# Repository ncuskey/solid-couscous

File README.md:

# Christmas Lockboxes 🎄🔐

A distributed, synchronized Narrative Escape Room experience powered by ESP32, MQTT, and Web Technologies.

## 🚀 Features (V2 Release - Christmas 2024)

### 🎙️ Radio Play System
- **Synchronized Audio**: Three boxes play character-specific audio tracks in perfect sync
- **MQTT Coordination**: All boxes receive `play_intro` command and start playback after 2-second sync delay
- **ESP-NOW Backup**: Conductor (Box 1) can broadcast low-latency sync signals
- **Character Mapping**:
  - Box 1 = Sam (Conductor)
  - Box 2 = Kristine
  - Box 3 = Jacob

### 🎭 Radio Play Controller
- **`radio_play.html`**: Web interface for triggering synchronized playback
  - "Play on Boxes" - Sends MQTT command to all physical boxes
  - "Play All (Browser)" - Preview all tracks in browser
  - Individual track playback for testing
  - Live dialogue display with timestamps

### 🔌 Power Management
- **Smart Standby**: WiFi sleep disabled for audio streaming stability
- **Amp Shutdown**: Pin D14 controls MAX98357A enable/disable
- **LED Brightness Cap**: Hard limit at 50 (20%) to prevent brownouts

### 🏥 Health & Reliability
- **Self-Test**: Startup check for WiFi RSSI (> -75dBm)
- **Visual Feedback**:
    - 🟢🟢🟢 Green Pulse = Ready
    - 🔴🔴🔴 Red Pulse = Weak Signal / Error
- **OTA Updates**: All boxes support over-the-air firmware updates (password: `admin`)

## Hardware Config
- **Lockbox 1 (Sam)**: 192.168.7.199 (Conductor)
- **Lockbox 2 (Kristine)**: 192.168.7.201
- **Lockbox 3 (Jacob)**: 192.168.7.202
- **Server**: `167.172.211.213` (MQTT + Web)
- **MQTT Port:** 1883 (Device), 9001 (WebSockets)
- **Web App:** `http://167.172.211.213/xmasLockboxes/`
- **Radio Play:** `http://167.172.211.213/xmasLockboxes/radio_play.html`
- **Admin Panel:** `http://167.172.211.213/xmasLockboxes/admin.html`

## Setup for Multiple Boxes

### Firmware Configuration
Edit `ChristmasLockbox/ChristmasLockbox.ino` lines 34-36:
```cpp
// Box 1 = Sam (CONDUCTOR), Box 2 = Kristine, Box 3 = Jacob
const char* box_topic_cmd = "lockbox/1/cmd";    // Change 1 to 2 or 3
const char* box_topic_status = "lockbox/1/status";
const char* client_id = "box_1_v2";             // Change to box_2_v2 or box_3_v2
```

### OTA Firmware Update
```bash
# Compile
/opt/homebrew/bin/arduino-cli compile --fqbn esp32:esp32:esp32 \
  --libraries /path/to/xmasLockboxes/libraries \
  --output-dir /path/to/xmasLockboxes/ChristmasLockbox/build \
  /path/to/xmasLockboxes/ChristmasLockbox/ChristmasLockbox.ino

# Upload (replace IP with target box)
/opt/homebrew/bin/arduino-cli upload -p 192.168.7.199 \
  --fqbn esp32:esp32:esp32 \
  -i /path/to/xmasLockboxes/ChristmasLockbox/build/ChristmasLockbox.ino.bin \
  --upload-field password=admin
```

## Deployment
Deploy web updates to server:
```bash
scp -i ssh -r www/* root@167.172.211.213:/var/www/xmasLockboxes/
```

## Audio Files
Radio play audio files (in `www/audio/`):
- `Intro_Sam.mp3` - Box 1 character audio (Sam's lines only)
- `Intro_Kristine.mp3` - Box 2 character audio (Kristine's lines only)
- `Intro_Jacob.mp3` - Box 3 character audio (Jacob's lines only)

Timeline:
- 0-10s: Power-up sounds
- 10-15s: Settling/ambient
- 15s+: Dialogue begins (see `show_sequence.json` for exact timestamps)

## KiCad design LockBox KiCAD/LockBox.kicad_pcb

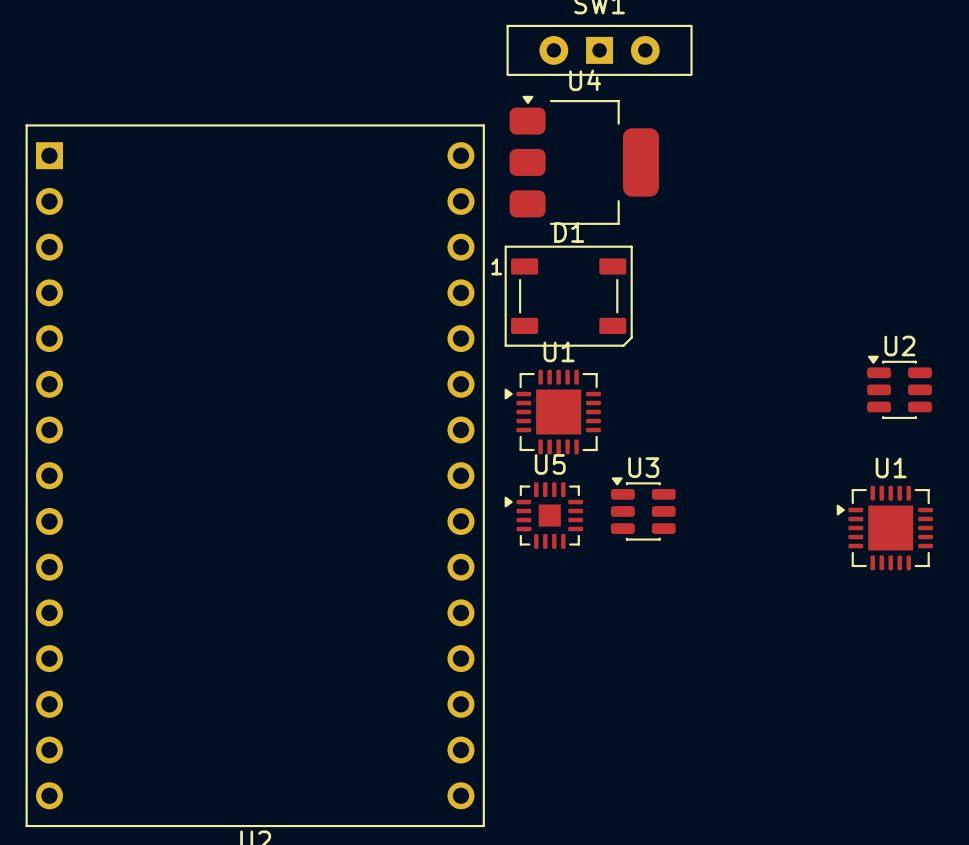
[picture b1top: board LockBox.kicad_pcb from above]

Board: 2 copper layers, 9 parts (0 on the bottom side), 10 nets, no tracks yet.

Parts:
D1: WS2812B; LED_WS2812B_PLCC4_5.0x5.0mm_P3.2mm
SW1: Power; SW_Slide-03_Wuerth-WS-SLTV_10x2.5x6.4_P2.54mm
U1, U1#2: MCP73871; QFN-20-1EP_4x4mm_P0.5mm_EP2.5x2.5mm
U2, U3: AP63203WU; TSOT-23-6
U2#2: ESP32-C3-DevKitM-1
U4: AMS1117-3.3; SOT-223-3_TabPin2
U5: MAX98357A; TQFN-16-1EP_3x3mm_P0.5mm_EP1.23x1.23mm

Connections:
/BAT+: U1.14 (V_{BAT}), U1.15 (V_{BAT})
/VBAT: U1#2.14 (V_{BAT}), U1#2.15 (V_{BAT}), U1#2.16 (V_{BAT_SENSE})
/VIN: U1.18 (IN), U1.19 (IN)
/VSYS: SW1.2 (C), U1.1 (OUT), U1.20 (OUT), U2.2 (EN), U2.3 (IN), U2#2.13 (5V), U2#2.14 (5V)
GND: U1.10 (V_{SS}), U1.11 (V_{SS}), U1.21 (V_{SS}), U1#2.5 (THERM), U1#2.9 (~TE), U1#2.10 (V_{SS}), U1#2.11 (V_{SS}), U1#2.21 (V_{SS}), U2.4 (GND), U2#2.1 (GND), U2#2.6 (GND), U2#2.8 (GND), U2#2.12 (GND), U2#2.15 (GND), U2#2.16 (GND), U2#2.19 (GND), U2#2.24 (GND), U2#2.27 (GND), U2#2.30 (GND)
unnamed: U2#2.2 (3V3), U2#2.3 (3V3)
unnamed: SW1.1 (B), U1#2.1 (OUT), U1#2.20 (OUT)
unnamed: U5.3 (GND), U5.11 (GND), U5.15 (GND)
unnamed: U5.7 (VDD), U5.8 (VDD)
VBUS: U1#2.17 (CE), U1#2.18 (IN), U1#2.19 (IN)

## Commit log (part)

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2025-12-14 Initial commit: Christmas Lockbox project with MQTT remote access support
2025-12-14 Finalize MQTT integration: Fix JS cache issues, add Lockbox 2 config, update README
2025-12-14 feat: Add Distributed Audio Simulator, OTA Updates, and Sequencer logic - Firmware: Enable ArduinoOTA, add MODE_SPEAKING - Simulator: Add multi-box visualizer with amplitude reactivity - Web: Add Scr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
2025-12-15 feat: Finalize mobile polish and director mode - Add iOS home screen icon and meta tags - Update admin grid for mobile widths - Enable Director mode in simulator
2025-12-15 chore: V1 Engineering Release - Firmware: Added Health Checks (RSSI, Amp SD, LED Kill) - Docs: Updated README with Feature List (Power, Sync, Health) - System: Start-up Visual Cues (Green/Red)
2025-12-16 Fix scrolling issues and duplicate relay pin
2025-12-16 Complete Electromagnet Integration
    - Fixed 5V Relay control via Open Drain logic
    - Updated admin.html for mobile stability
    - Integrated puzzle win condition with physical unlock
    - Updated documentation
2025-12-20 Port firmware to ESP32: Add cross-platform headers, pin definitions, and update UDP print
2025-12-20 Add ESP32 verification sketch and toolchain config
2025-12-20 feat: optimize audio quality (streaming + DSP) and fix relay wiring
2025-12-20 Update firmware for solenoid migration and add documentation
2025-12-23 feat: complete toy factory gameplay overhaul with infinite belt, balanced item generation, and refined claw mechanics
2025-12-23 feat: implement start screen with zoom transition
2025-12-23 style: refine start screen with glittering click zone
2025-12-23 chore: align click zone perfectly with fixed tool background
2025-12-23 Refactor apps: 5-digit themed keypads for Sam, Kristine, Jacob
2025-12-23 Synchronize audio and light show with correct mapping and transcripts
2025-12-24 Final solenoid migration: 500ms pulse, updated power docs
2025-12-24 Fix audio interference (Hardwire SD) and Solenoid Brownout (Remove LED Flash)
2025-12-24 Final fleet update: Configured for Box 1, 5.0s pulse active
2025-12-24 Add Finale audio tracks to admin interface
2025-12-24 Remove unused audio assets (Tink/Pip/Bram) and clean up admin interface
2025-12-24 docs: update walkthrough and task list with audio sync progress
2025-12-25 feat: Implement Onboard Audio (SPIFFS) and Fix Sync Logic
    - Converted firmware to use SPIFFS for audio playback (zero latency).
    - Updated radio_play.html to send individual start commands to all boxes.
    - Fixed firmware client_id checks to correctly assign colors (Sam/Kris/Jacob).
    - Optimized all audio files to 64kbps mono for reliability.
    - Verified on hardware.
2025-12-25 assets: Add final 120s master audio files for Sam, Kristine, and Jacob
2025-12-25 fix: Remove flaky confirmation dialogs from admin.html and verify GPIO 33 for lock
